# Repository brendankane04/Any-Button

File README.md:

# Any Button
With this device, you can make any pushbutton or switch on a home appliance *remote controlled!* 

Simply connect the leads of the button of the appliance to the relay on this device, and it will make the device remote-operated.

## Materials:

1. [VS1838 IR Receiver](https://datasheetspdf.com/pdf-file/700398/ETC/VS1838B/1) <br>
2. [IR Remote (MP3 Control)](https://www.amazon.com/KOOBOOK-Infrared-Wireless-Control-Receiver/dp/B07S67SFSF/ref=pd_sbs_1/140-3142093-1069413?pd_rd_w=dmh5y&pf_rd_p=0a3ad226-8a77-4898-9a99-63ffeb1aef90&pf_rd_r=679X1BYENFA4Q5D7KPQT&pd_rd_r=20a569e2-5dc0-4ce2-99c9-b3cc044566fd&pd_rd_wg=Kmetr&pd_rd_i=B07S67SFSF&psc=1) <br>
3. [Attiny85, DIP package](https://www.amazon.com/Original-Atmel-Dip-8-ATTINY85-20PU-Tiny85-20Pu/dp/B06W9JBJJ6/ref=sr_1_3?dchild=1&keywords=attiny85&qid=1628904159&sr=8-3) <br>
4. [L7805 5V Voltage regulator](https://www.amazon.com/Pieces-Voltage-Regulator-Linear-Positive/dp/B07RB251DC/ref=sr_1_4?dchild=1&keywords=L7805&qid=1628904211&sr=8-4) <br>
5. Various Electical Components <br> 

## Firmware: 

This file system is a project which can be conveniently opened in Atmel Studio 7 with the following important source files:

### Files:

-**main.cpp:** Main file<br>
-**IR_Receiver.cpp:** Driver for the IR Receiver connected to the INT0 pin. It receives IR commands based on the IR-NEC protocol<br>
-**Relay.cpp:** Driver for the relay which simulates the switch or button<br>
-**Lever.cpp:** Driver for a relay which controls a solenoid attached to a lever. This requires more physical set up & hardware but doesn't necessitate directly wiring to the appliance.<br>
-**BB\_I2C.cpp:** Driver for a rudimentary pseudo-I2C communication protocol. It was written to make debugging easier.<br>

## Schematics:

This file system contains a project which builds the schematic design & the board layout of the device. 
The project can opened with kicad.

The device may be connected to the appliance by attaching a >= 5V line or by using an independent voltage source.

It uses default parts & layouts. Consequently, it has no custom libraries.

The final product can be conveniently viewed in the form of PDF's

### PDF's:

-**Schematic.pdf:** Image of the schematics <br>
<br>
-**Layout.pdf:** Image of the board layout <br>
<br>

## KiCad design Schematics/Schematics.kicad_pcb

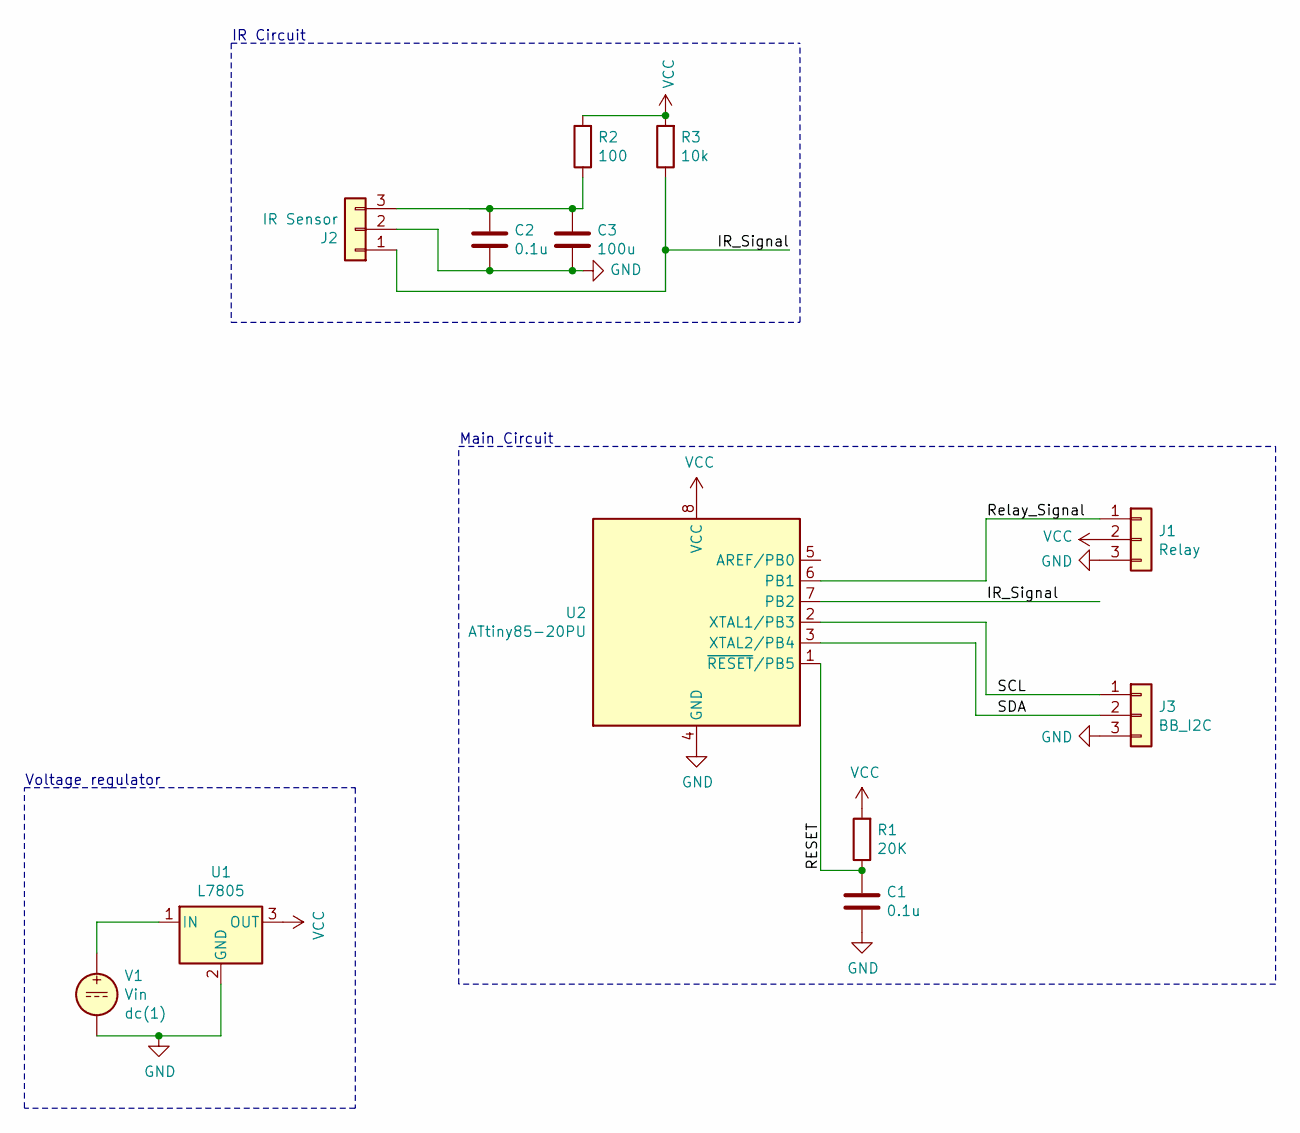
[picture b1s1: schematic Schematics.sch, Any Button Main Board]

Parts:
C1, C2: 0.1u; C_Disc_D3.0mm_W1.6mm_P2.50mm
C3: 100u; C_Disc_D3.0mm_W1.6mm_P2.50mm
J1: Relay; PinHeader_1x03_P2.54mm_Vertical
J2: IR Sensor; PinHeader_1x03_P2.54mm_Vertical
J3: BB_I2C; PinHeader_1x03_P2.54mm_Vertical
R1: 20K; R_Axial_DIN0204_L3.6mm_D1.6mm_P1.90mm_Vertical
R2: 100; R_Axial_DIN0204_L3.6mm_D1.6mm_P1.90mm_Vertical
R3: 10k; R_Axial_DIN0204_L3.6mm_D1.6mm_P1.90mm_Vertical
U1: L7805; PinHeader_1x03_P2.54mm_Vertical
U2: ATtiny85-20PU; DIP-8_W7.62mm
V1: Vin; PinHeader_1x02_P2.54mm_Vertical

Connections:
/IR_Signal: J2.1, R3.1, U2.7 (PB2)
/RESET: C1.1, R1.1, U2.1 (~RESET~/PB5)
/Relay_Signal: J1.1, U2.6 (PB1)
/SCL: J3.1, U2.2 (XTAL1/PB3)
/SDA: J3.2, U2.3 (XTAL2/PB4)
GND: C1.2, C2.2, C3.2, J1.3, J2.2, J3.3, U1.2 (GND), U2.4 (GND), V1.2; also elsewhere on the board
unnamed: C2.1, C3.1, J2.3, R2.1
unnamed: U1.1 (IN), V1.1
VCC: J1.2, R1.2, R2.2, R3.2, U1.3 (OUT), U2.8 (VCC); also elsewhere on the board

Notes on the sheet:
Voltage regulator
Main Circuit
IR Circuit

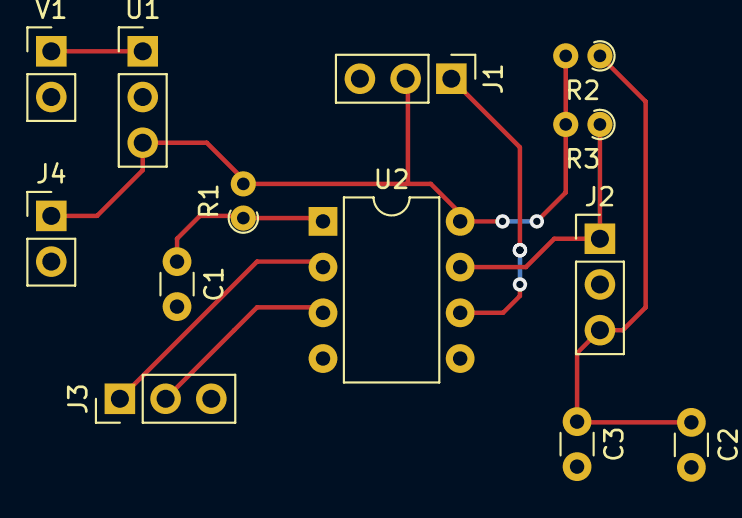
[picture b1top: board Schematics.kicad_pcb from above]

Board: 2 copper layers, 13 parts (0 on the bottom side), 9 nets.

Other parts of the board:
J4: Conn_01x02; PinHeader_1x02_P2.54mm_Vertical

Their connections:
GND: J4.2; also elsewhere on the board
VCC: J4.1; also elsewhere on the board

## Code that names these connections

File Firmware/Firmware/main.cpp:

//Remote Control Receiver Momentary+Alternate Original ATtiny13A 20191021 2200
//PB1,PB2 : Momentary Operation
//PB3,PB4 : Alternate Operation

#ifndef F_CPU
#define F_CPU 8000000UL
#endif 

#include <avr/io.h>
#include <avr/interrupt.h>
#include <util/delay.h>
#include "IR_Receiver.h"
#include "Relay.h"

#define FALSE 0
#define TRUE  1

int main(void)
{
	IR_Receiver sensor1(7);
	Relay button1(1);

	//Initialize an empty IR command
	IR_Receiver::IR_cmd remote_cmd;

	while(1)
	{
		remote_cmd = sensor1.recv();
		switch(remote_cmd.cmd)
		{
			case IR_Receiver::POWER:
				button1.press();
				break;
			case IR_Receiver::ZERO:
				button1.button_set(FALSE);
				break;
			case IR_Receiver::ONE:
				button1.button_set(TRUE);
				break;
			default:
				break;
		}
		_delay_ms(10);
	}
}

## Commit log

2021-06-24 The external code was modified to allow for compiling.
2021-06-25 The README was added.
2021-06-28 README change
2021-06-28 Testing was done.
2021-06-28 A different reference for IR code was used.
2021-06-30 External IR decoder files were added.
2021-06-30 A basic working model of the IR receiver NEC decoder was established.
2021-07-01 A function for waiting for the pin to change & recording the wait time was created from scratch.
2021-07-01 Template function code for the IR receiver was added.
2021-07-03 A IR command receiving function was written.
2021-07-03 USI commands were added for debugging.
2021-07-05 The system clock frequency was increased.
2021-07-06 An object for the IR Receiver was created.
2021-07-07 Removed bug in recv() which would cause all comparisons to fail.
2021-07-07 A relay class was added to control the relay with toggling & sets. However, it needs to be tested.
2021-07-07 Interrupt enabling was removed.
2021-07-07 The bit-banged pseudo-I2C functionality was modularized into a BB_I2C class.
2021-07-08 The classes were exported to external files for encapsulation.
2021-07-10 The external classes were actually added in git.
2021-07-11 Quality of life improvements for the relay code.
2021-07-12 The README was updated.
2021-07-12 The README was normalized to the rest of my READMEs.
2021-07-14 The IR Reciever code was altered to read from any arbitrary PCINTX pin. Testing is required.
2021-07-14 The speed of the system clock was increased when attaching IR sensor.
2021-07-16 A button was made more obvious.
2021-07-16 A format error was fixed.
2021-07-16 The relay controls were moved to modularized functions in case other relays work differently.
2021-07-16 the gitignore file was created
2021-07-17 The materials section was updated.
2021-07-18 A delay was added to the main loop to improve latency.
2021-07-20 An alignment error was fixed.
2021-07-20 A quality of life change was made.
2021-07-20 A schematics directory was created.
2021-07-22 A rudimentary schematic was created.
2021-07-22 The circuitry for the reset line was added.
2021-07-22 Footprints for various connectors were added,
2021-07-22 The schematics were sectioned off.
2021-07-22 Footprints for the voltage regulator were picked.
2021-07-22 The net list was generated. It needs work though. The decoupling capcitor also needs a smaller footprint. It's about as large as the ATTINY. That's excessive.
2021-07-22 The capictor's footprint was shrunk.
2021-07-22 The basic routes were finished.
2021-07-22 A silkscreen was added.
2021-07-22 A simpler cutout of the board was made.
2021-07-22 The title block was modified, and a PDF of the layout was made.
2021-07-22 A PDF of the schematic was made.
2021-07-22 The new files were actually added.
2021-07-26 Binaries were removed.
2021-07-28 A class for controlling solenoids via a relay was added.
2021-08-01 The compatibility circuit for the IR Receiver was added to the schematics.
2021-08-01 An error was correct, and the board was updated. Adjustments are still necessary.
2021-08-03 A change was rolled back.
2021-08-07 The IR circuit was added to the layout.
2021-08-08 The PDF's were updated.
2021-08-10 The schematic was updated.
2021-08-11 The debugging output was removed from main.
2021-08-13 A link was added to the documentation.
2021-08-15 Erroneous code was commented out. However, errors persist.
2021-08-15 By fixing up the firmware & hardware, the project is back to a working state.
2021-08-15 A timing error was fixed.
2021-08-15 Quality of life changes were made.
2021-08-16 A capacitor value was changed.
2021-08-18 Some error messages were improved.
2021-08-20 The other buttons on the remote were added.
2021-08-22 Unnecessary default constructors were removed.
2021-08-23 Another default constructor was removed.
2021-08-24 A new listening function was started.
2021-08-25 The listening function was developed.
2021-08-25 A table was finished.
2021-08-26 A battery input was added for lower voltages.
2021-08-27 A header was removed.
2021-12-08 .bak files removed
2022-01-06 Update README.md
    README update
2023-01-22 Update README.md
    included images in the README
2023-01-22 png's added
2023-01-22 Update README.md
    PDF's in README converted to PNG's
2023-01-22 Layout image recropping
